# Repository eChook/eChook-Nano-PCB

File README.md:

# eChook Nano PCB

This is the RS DesignSpark PCB project file and associated gerber files and BOM for the eChook Nano PCB v1.1

eChook Specific Libraries not included yet.

Designspark 8 required

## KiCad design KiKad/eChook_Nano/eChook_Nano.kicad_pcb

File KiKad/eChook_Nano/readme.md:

V2.0a issues:
- Op Amp inputs switched. -FIXED 26/09
- TP Vias too small to capture multimeter probe tip. Fixed 26/09
- RPM inputs not working??
- No 24v power LED

V2.0b TODO
- Add 24v Indicator LED
- Make Throttle input 24v safe - 24mA through 200mA capable diode - TEST!
- THT Pads enlarged
- keep out zone around BT Mount point
- Totem Pole BAT54S diode protection on all inputs
-

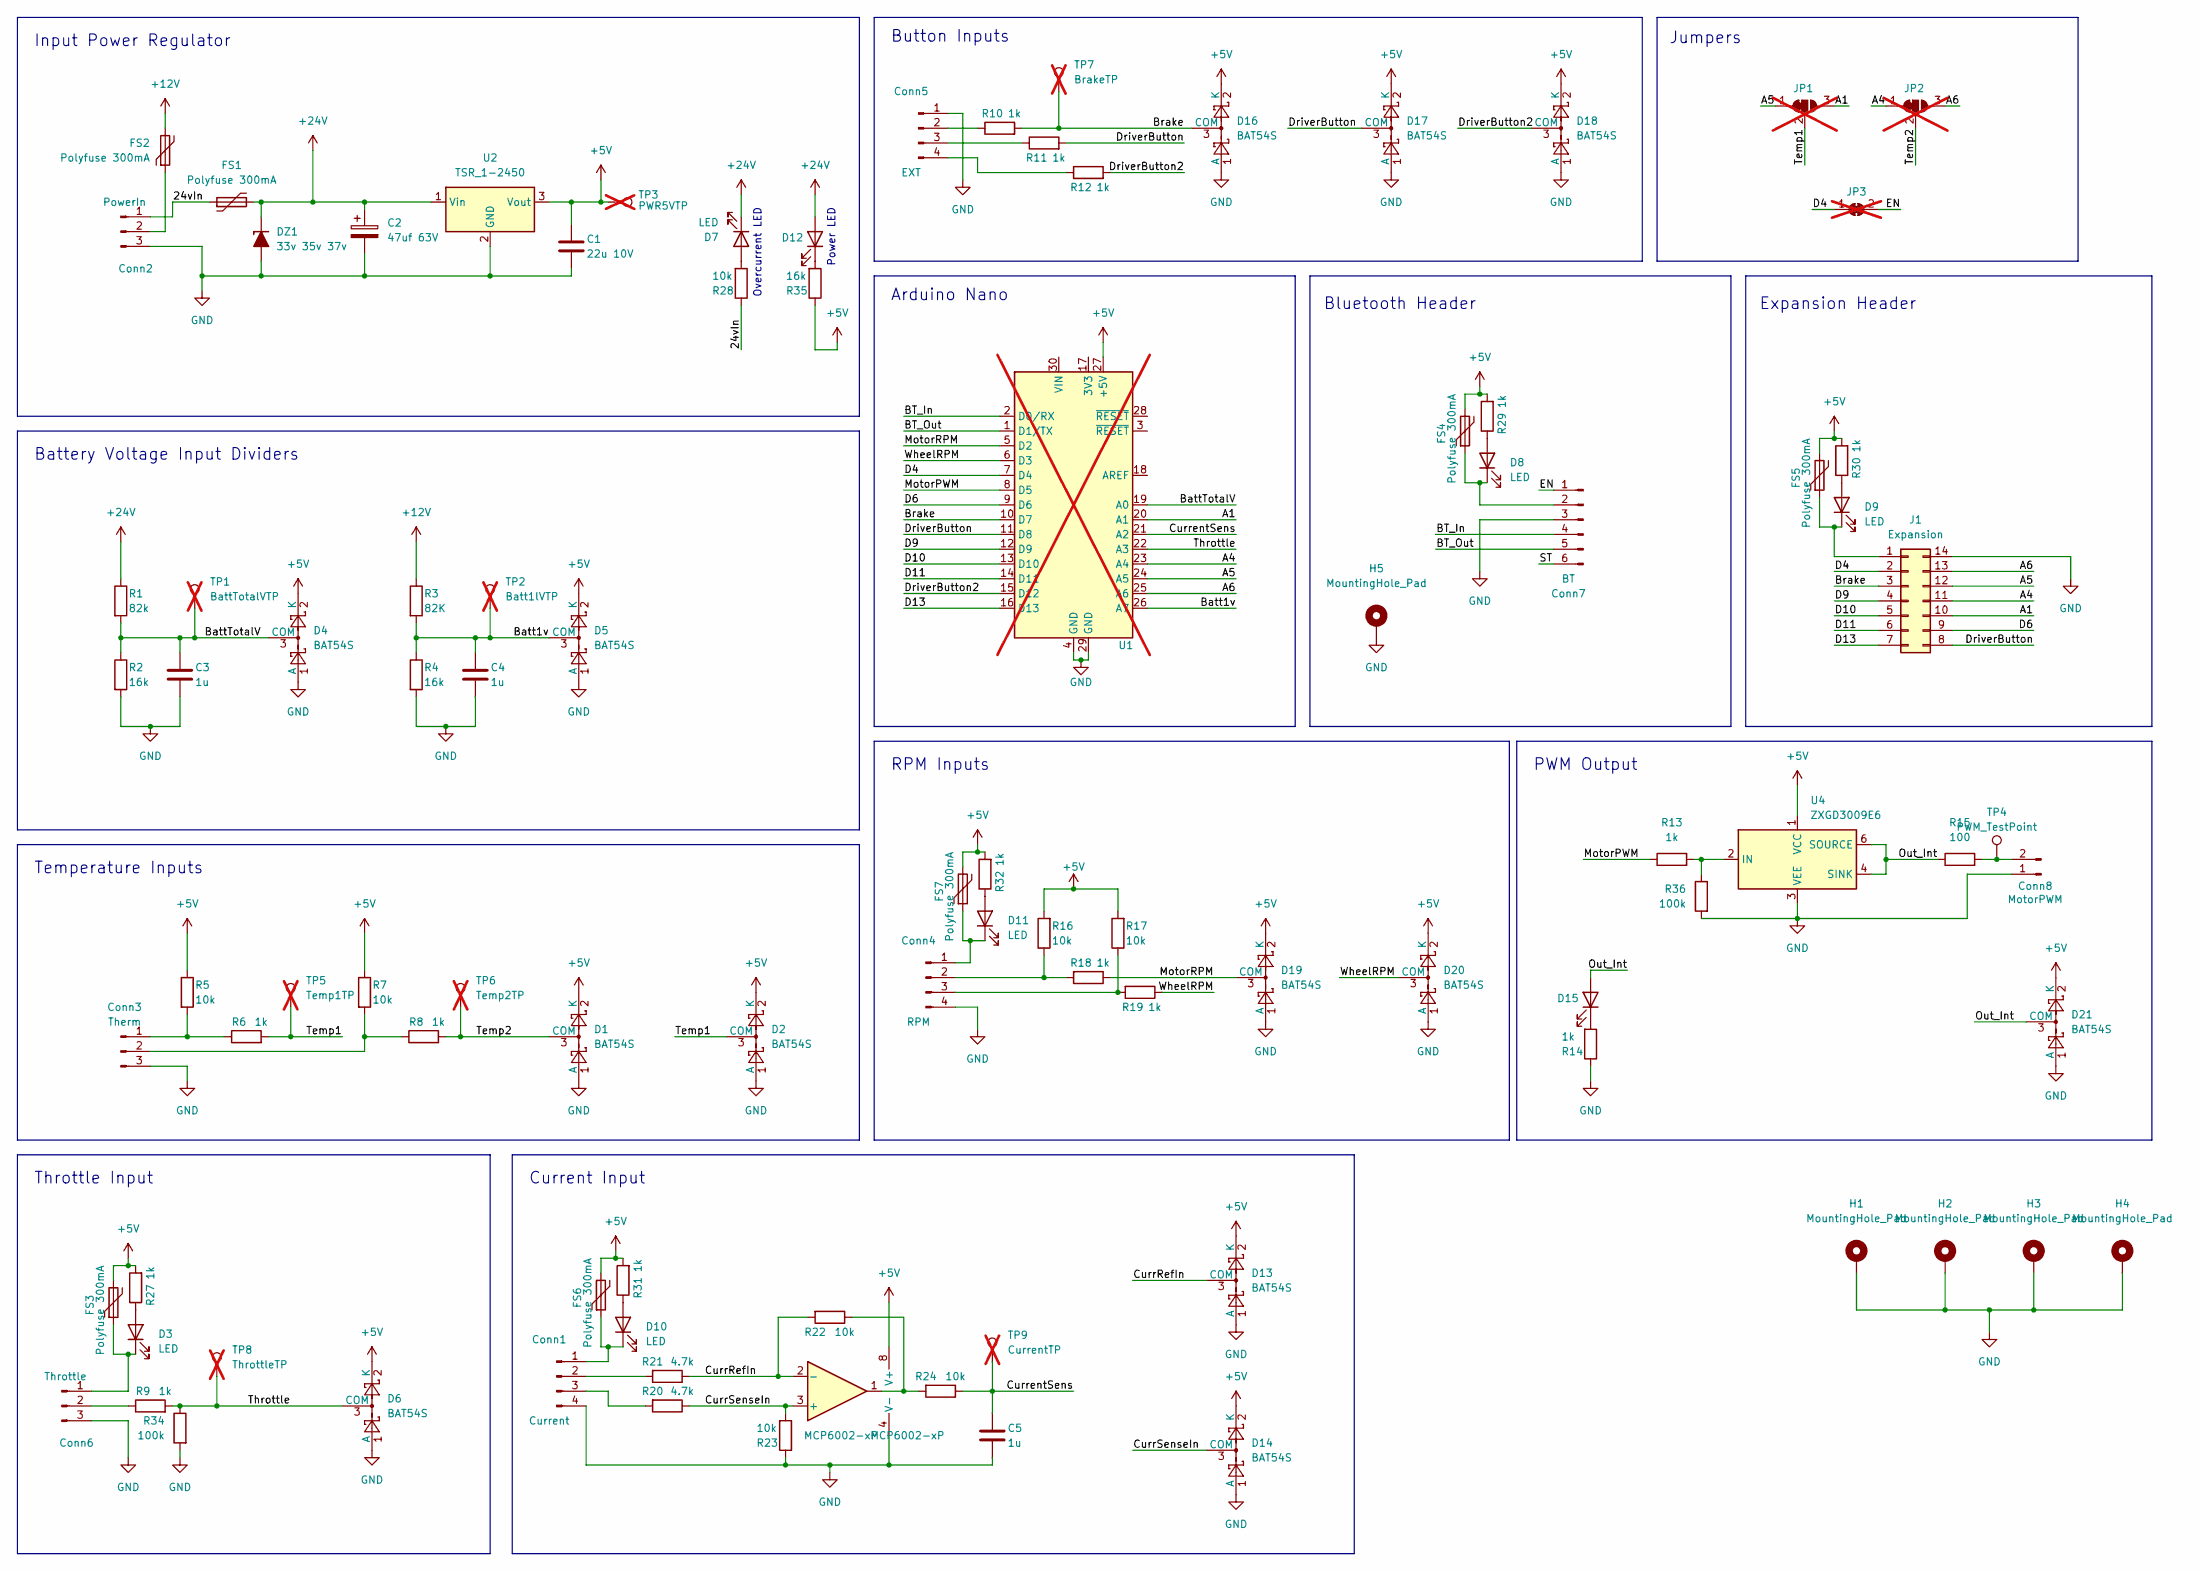
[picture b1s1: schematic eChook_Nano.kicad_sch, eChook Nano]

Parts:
C1: 22u 10V; C_0805_2012Metric; LCSC C45783
C2: 47uf 63V; CP_Elec_10x10; MPN EEEHA1J470P; LCSC C125977
C3, C4, C5: 1u; C_0805_2012Metric; LCSC C28323
Conn1: Current; Pluggable_Terminal_4_5.08mm; LCSC C8443
Conn2: PowerIn; Pluggable_Terminal_3_3.81mm; LCSC C8406
Conn3: Therm; Pluggable_Terminal_3_5.08mm; LCSC C70914
Conn4: RPM; Pluggable_Terminal_4_5.08mm; LCSC C8443
Conn5: EXT; Pluggable_Terminal_4_5.08mm; LCSC C8443
Conn6: Throttle; Pluggable_Terminal_3_5.08mm; LCSC C70914
Conn7: BT; PinHeader_1x06_P2.54mm_Vertical; LCSC C5224026
Conn8: MotorPWM; Pluggable_Terminal_2_5.08mm; LCSC C441204
D1, D2, D4, D5, D6, D13, D14, D16, D17, D18, D19, D20, D21: BAT54S; SOT-23; MPN BAT54S,215; LCSC C47546
D3, D7, D8, D9, D10, D11: LED; LED_0603_1608Metric; LCSC C2286
D12, D15: LED_GREEN; LED_0805_2012Metric; MPN KT-0805G; LCSC C2297
DZ1: 33v 35v 37v; D_SMB; MPN PTZTE2533B; LCSC C2909283
FS1, FS2, FS3, FS4, FS5, FS6, FS7: Polyfuse 300mA; Fuse_0603_1608Metric; MPN BHFUSE BSMD0603-010-36V; LCSC C7472522
H1, H2, H3, H4: MountingHole_Pad; MountingHole_3.2mm_M3_DIN965_Pad_TopBottom
H5: MountingHole_Pad; MountingHole_4.3mm_M4_DIN965_Pad
J1: Expansion; PinHeader_2x07_P2.54mm_Vertical; LCSC C38844
JP1, JP2: SolderJumper_3_Bridged12; SolderJumper-3_P1.3mm_Bridged12_RoundedPad1.0x1.5mm; not fitted
JP3: SolderJumper-2_P1.3mm_Bridged_RoundedPad1.0x1.5mm; not fitted
R1: 82k; R_0805_2012Metric; LCSC C21571501
R2, R4, R35: 16k; R_0805_2012Metric; LCSC C706220
R3: 82K; R_0805_2012Metric; LCSC C21571501
R5, R7, R16, R17, R22, R23, R24, R28: 10k; R_0805_2012Metric; LCSC C17414
R6, R8, R9, R10, R11, R12, R14, R18, R19, R27, R29, R30, R31, R32: 1k; R_0805_2012Metric; LCSC C17513
R13: 1k; R_0805_2012Metric; LCSC C17414
R15: 100; R_0805_2012Metric; LCSC C17414
R20, R21: 4.7k; R_0805_2012Metric; LCSC C17673
R34, R36: 100k; R_0805_2012Metric; LCSC C149504
TP1: BattTotalVTP; TestPoint_Pad_D3.0mm; not fitted
TP2: Batt1lVTP; TestPoint_Pad_D3.0mm; not fitted
TP3: PWR5VTP; TestPoint_Pad_D3.0mm; not fitted
TP4: PWM_TestPoint; TestPoint_Pad_D3.0mm
TP5: Temp1TP; TestPoint_Pad_D3.0mm; not fitted
TP6: Temp2TP; TestPoint_Pad_D3.0mm; not fitted
TP7: BrakeTP; TestPoint_Pad_D3.0mm; not fitted
TP8: ThrottleTP; TestPoint_Pad_D3.0mm; not fitted
TP9: CurrentTP; TestPoint_Pad_D3.0mm; not fitted
U1: Arduino_Nano_v3.x; Arduino_Nano; not fitted
U2: TSR_1-2450; Converter_DCDC_TRACO_TSR-1_THT; LCSC C19188491
U3: MCP6002-xP; SOIC-8_3.9x4.9mm_P1.27mm; LCSC C7377
U4: ZXGD3009E6; SOT-23-6; LCSC C156293

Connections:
+5V: C1.1, D1.2 (K), D2.2 (K), D4.2 (K), D5.2 (K), D6.2 (K), D13.2 (K), D14.2 (K), D16.2 (K), D17.2 (K), D18.2 (K), D19.2 (K), D20.2 (K), D21.2 (K), FS3.2, FS4.2, FS5.2, FS6.2, FS7.2, R5.1, R7.1, R16.2, R17.2, R27.2, R29.2, R30.2, R31.2, R32.2, R35.1, TP3.1, U1.27 (+5V), U2.3 (Vout), U3.8 (V+), U4.1 (VCC)
+12V: FS2.2, R3.1
+24V: C2.1, D7.1 (K), D12.2 (A), DZ1.1 (K), FS1.2, R1.1, U2.1 (Vin)
/24vIn: Conn2.1, FS1.1, R28.1
/A1: J1.10, JP1.3 (B), U1.20 (A1)
/A4: J1.11, JP2.1 (A), U1.23 (A4)
/A5: J1.12, JP1.1 (A), U1.24 (A5)
/A6: J1.13, JP2.3 (B), U1.25 (A6)
/BT_In: Conn7.4, U1.2 (D0/RX)
/BT_Out: Conn7.5, U1.1 (D1/TX)
/Batt1v: C4.1, D5.3 (COM), R3.2, R4.1, TP2.1, U1.26 (A7)
/BattTotalV: C3.1, D4.3 (COM), R1.2, R2.1, TP1.1, U1.19 (A0)
/Brake: D16.3 (COM), J1.3, R10.2, TP7.1, U1.10 (D7)
/CurrRefIn: D13.3 (COM), R21.1, R22.2, U3.2 (-)
/CurrSenseIn: D14.3 (COM), R20.1, R23.2, U3.3 (+)
/CurrentSens: C5.1, R24.1, TP9.1, U1.21 (A2)
/D4: J1.2, JP3.1 (A), U1.7 (D4)
/D6: J1.9, U1.9 (D6)
/D9: J1.4, U1.12 (D9)
/D10: J1.5, U1.13 (D10)
/D11: J1.6, U1.14 (D11)
/D13: J1.7, U1.16 (D13)
/DriverButton: D17.3 (COM), J1.8, R11.2, U1.11 (D8)
/DriverButton2: D18.3 (COM), R12.2, U1.15 (D12)
/EN: Conn7.1, JP3.2 (B)
/MotorPWM: R13.1, U1.8 (D5)
/MotorRPM: D19.3 (COM), R18.1, U1.5 (D2)
/Out_Int: D15.2 (A), D21.3 (COM), R15.1, U4.4 (SINK), U4.6 (SOURCE)
/ST: Conn7.6
/Temp1: D2.3 (COM), JP1.2 (C), R6.2, TP5.1
/Temp2: D1.3 (COM), JP2.2 (C), R8.2, TP6.1
/Throttle: D6.3 (COM), R9.2, R34.1, TP8.1, U1.22 (A3)
/WheelRPM: D20.3 (COM), R19.1, U1.6 (D3)
GND: C1.2, C2.2, C3.2, C4.2, C5.2, Conn1.4, Conn2.3, Conn3.3, Conn4.4, Conn5.1, Conn6.3, Conn7.3, Conn8.1, D1.1 (A), D2.1 (A), D4.1 (A), D5.1 (A), D6.1 (A), D13.1 (A), D14.1 (A), D16.1 (A), D17.1 (A), D18.1 (A), D19.1 (A), D20.1 (A), D21.1 (A), DZ1.2 (A), H1.1, H2.1, H3.1, H4.1, H5.1, J1.14, R2.2, R4.2, R14.1, R23.1, R34.2, R36.2, U1.4 (GND), U1.29 (GND), U2.2 (GND), U3.4 (V-), U4.3 (VEE)
unnamed: Conn1.1, D10.1 (K), FS6.1
unnamed: Conn1.2, R21.2
unnamed: Conn1.3, R20.2
unnamed: Conn2.2, FS2.1
unnamed: Conn3.1, R5.2, R6.1
unnamed: Conn3.2, R7.2, R8.1
unnamed: Conn4.1, D11.1 (K), FS7.1
unnamed: Conn4.2, R16.1, R18.2
unnamed: Conn4.3, R17.1, R19.2
unnamed: Conn5.2, R10.1
unnamed: Conn5.3, R11.1
unnamed: Conn5.4, R12.1
unnamed: Conn6.1, D3.1 (K), FS3.1
unnamed: Conn6.2, R9.1
unnamed: Conn7.2, D8.1 (K), FS4.1
unnamed: Conn8.2, R15.2, TP4.1
unnamed: D3.2 (A), R27.1
unnamed: D7.2 (A), R28.2
unnamed: D8.2 (A), R29.1
unnamed: D9.2 (A), R30.1
unnamed: D9.1 (K), FS5.1, J1.1
unnamed: D10.2 (A), R31.1
unnamed: D11.2 (A), R32.1
unnamed: D12.1 (K), R35.2
unnamed: D15.1 (K), R14.2
unnamed: R22.1, R24.2, U3.1
unnamed: R13.2, R36.1, U4.2 (IN)

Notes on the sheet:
Bluetooth Header
Input Power Regulator
Throttle Input
RPM Inputs
Arduino Nano
PWM Output
Power LED
Temperature Inputs
Current Input
Button Inputs
Overcurrent LED
Expansion Header
Jumpers
Battery Voltage Input Dividers

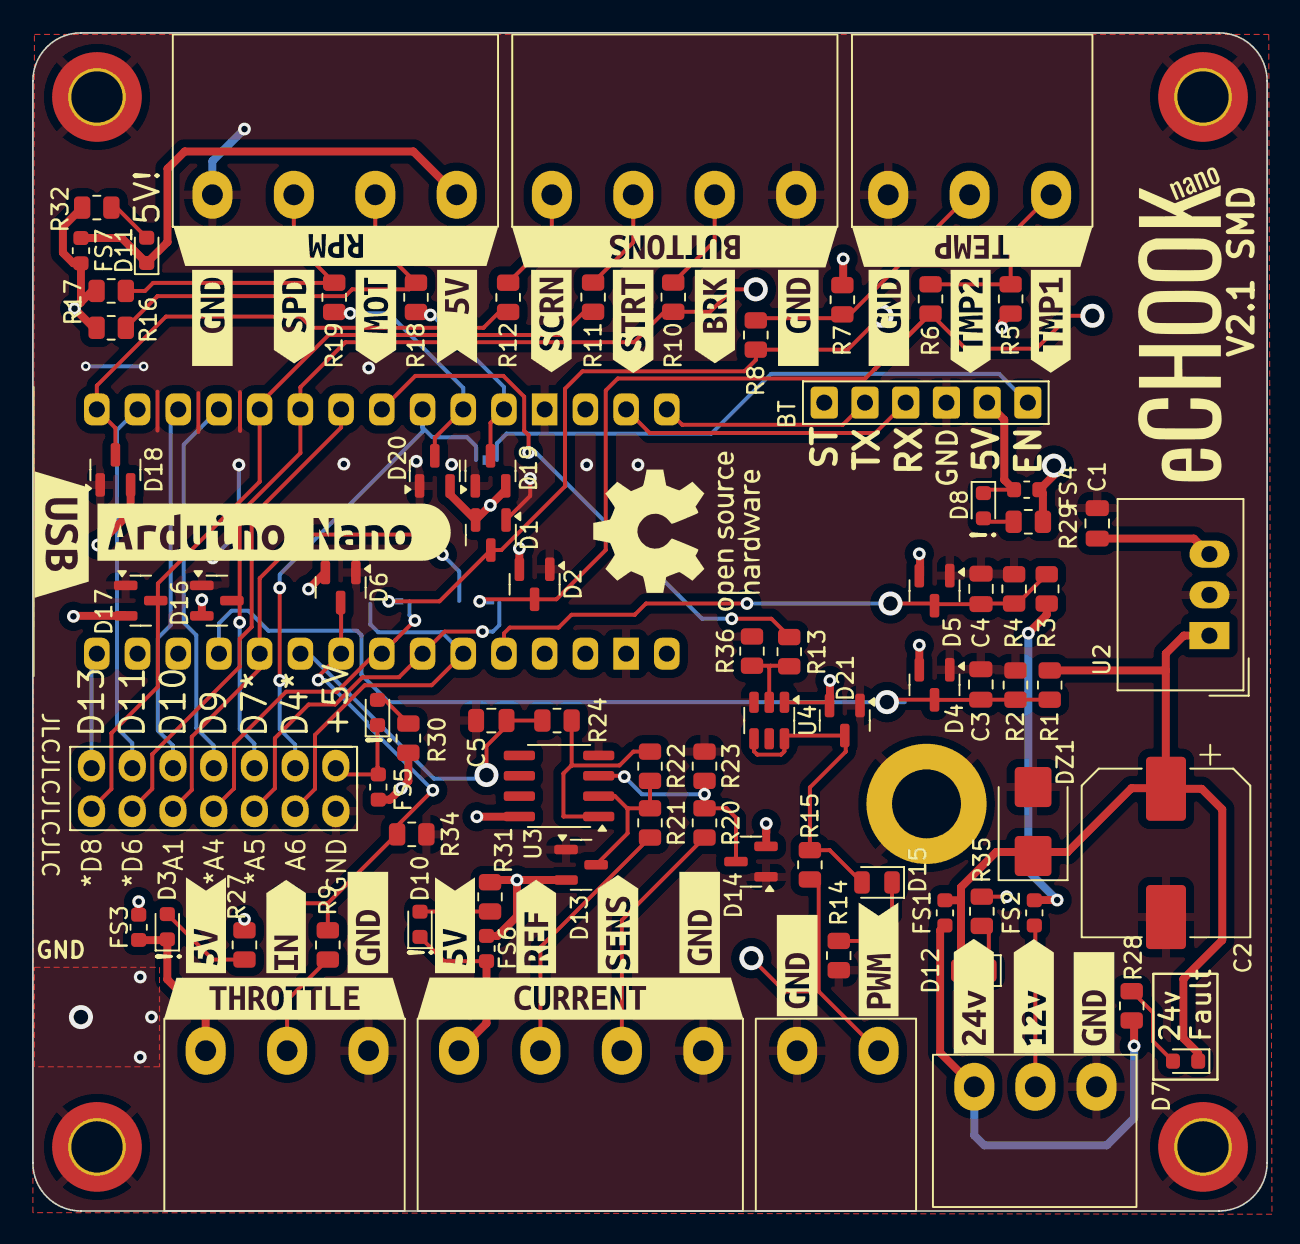
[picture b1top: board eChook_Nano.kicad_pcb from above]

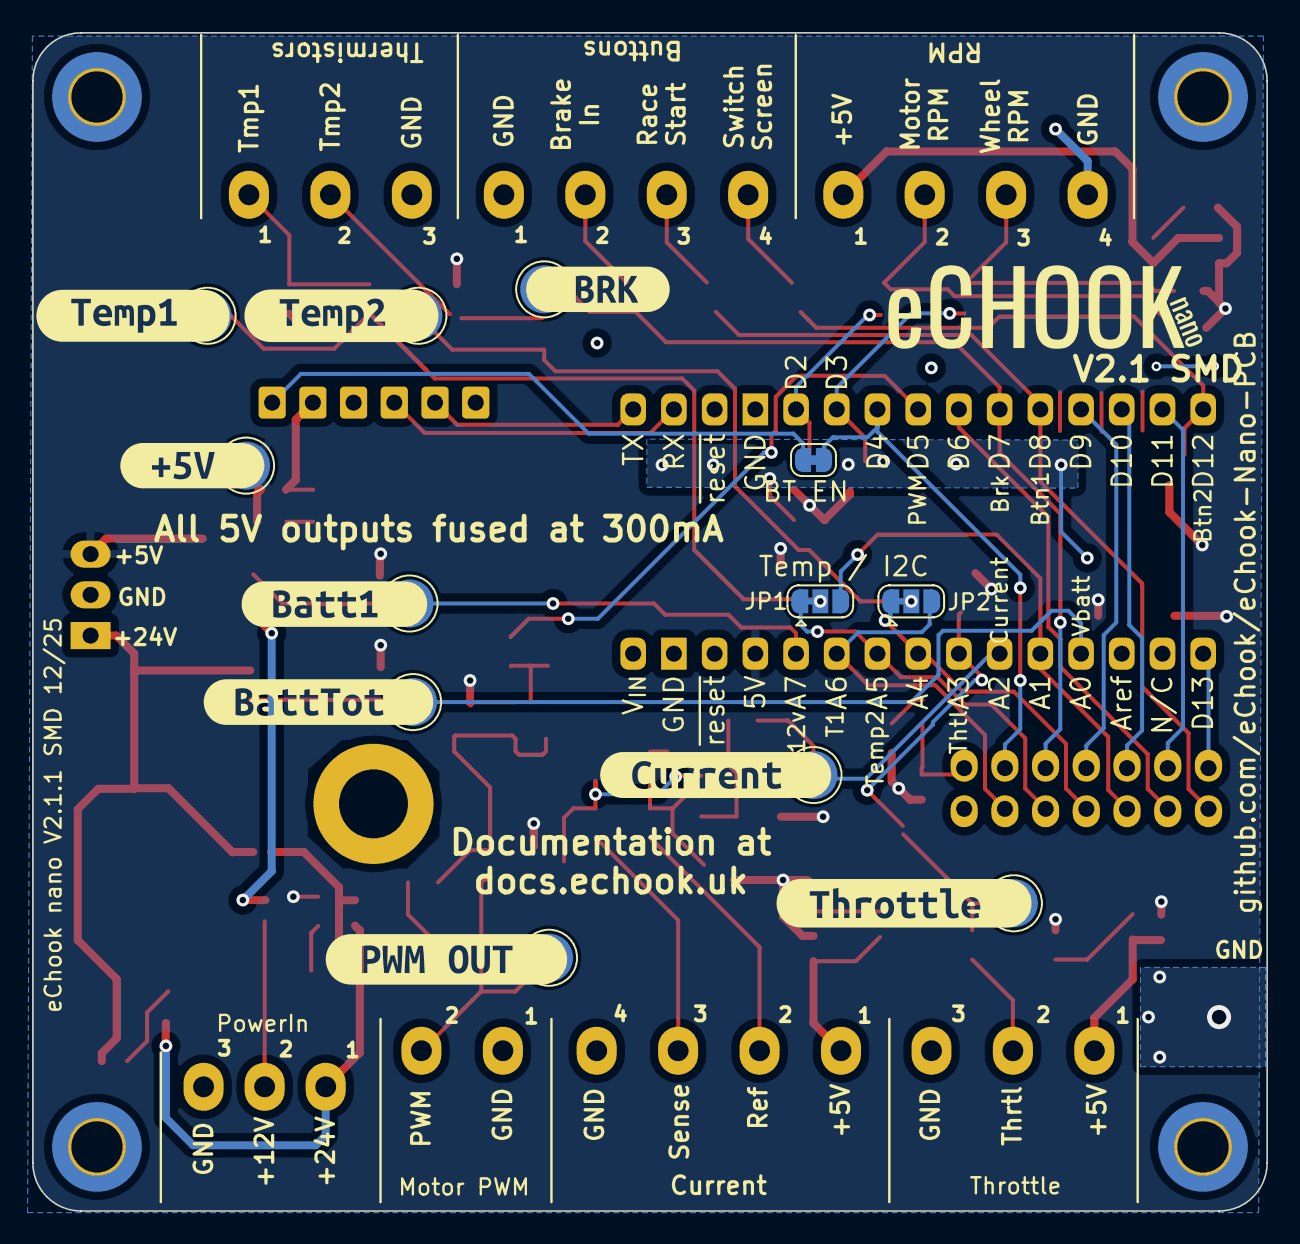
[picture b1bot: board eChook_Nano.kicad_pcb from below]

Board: 2 copper layers, 77.0 x 73.5 mm, 138 parts (21 on the bottom side), 60 nets.

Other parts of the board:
BC1, BC2: BOM-Component
kibuzzard-66D71FF8: G***; kibuzzard-66D71FF8
kibuzzard-66D72A35: G***; kibuzzard-66D72A35
kibuzzard-66D86D8A: G***; kibuzzard-66D86D8A
kibuzzard-66D86D91: G***; kibuzzard-66D86D91
kibuzzard-66D86E8F: G***; kibuzzard-66D86E8F
kibuzzard-66D86EA3: G***; kibuzzard-66D86EA3
kibuzzard-66D86EBA: G***; kibuzzard-66D86EBA
kibuzzard-66D86EDC: G***; kibuzzard-66D86EDC
kibuzzard-66D86F00: G***; kibuzzard-66D86F00
kibuzzard-66D86F2B: G***; kibuzzard-66D86F2B
kibuzzard-66D86F7C: G***; kibuzzard-66D86F7C
kibuzzard-66D86F40: G***; kibuzzard-66D86F40
kibuzzard-66D86F46: G***; kibuzzard-66D86F46
kibuzzard-66D86F51: G***; kibuzzard-66D86F51
kibuzzard-66D86F60: G***; kibuzzard-66D86F60
kibuzzard-66D727FC: G***; kibuzzard-66D727FC
kibuzzard-66D728C6: G***; kibuzzard-66D728C6
kibuzzard-66D728F7: G***; kibuzzard-66D728F7
kibuzzard-66D7200F: G***; kibuzzard-66D7200F
kibuzzard-66D7283F: G***; kibuzzard-66D7283F
kibuzzard-66D72019, kibuzzard-66D72019#2, kibuzzard-66D72019#3, kibuzzard-66D72019#4: G***; kibuzzard-66D72019
kibuzzard-66D72322: G***; kibuzzard-66D72322
kibuzzard-66D72613, kibuzzard-66D72613#2: G***; kibuzzard-66D72613
kibuzzard-66D72997: G***; kibuzzard-66D72997
kibuzzard-66E1D05B: G***; kibuzzard-66E1D05B
kibuzzard-66E1D172: G***; kibuzzard-66E1D172
kibuzzard-66E1DBD4: G***; kibuzzard-66E1DBD4
kibuzzard-66E1DC01: G***; kibuzzard-66E1DC01
kibuzzard-66E1DD3E: G***; kibuzzard-66E1DD3E
kibuzzard-66E1DD07: G***; kibuzzard-66E1DD07
kibuzzard-66E1DD26: G***; kibuzzard-66E1DD26
kibuzzard-66E1DDEC: G***; kibuzzard-66E1DDEC
kibuzzard-66E1DE80: G***; kibuzzard-66E1DE80
kibuzzard-66E1DE99: G***; kibuzzard-66E1DE99
kibuzzard-67D9A076: G***; kibuzzard-67D9A076

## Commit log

2017-06-07 initial commit of V1.1
2017-06-08 Added BOM
2017-07-06 Updated to latest PCB design
2017-07-28 V1.2 - improved solder mask tolerances, added test points and silkscreen logo
2017-08-23 Updated PCB Version in Readme
2017-09-04 Added GNU Licence.txt
2022-01-04 Restructured Filesystem. Started KiCad Recreation
2022-01-04 Add KiCad gitignore
2022-01-10 Finished PCB Replication, added iBOM
2022-01-12 Added 3D models and layout/silkscreen improvements
2022-01-12 Added 3D models
2022-01-15 Fixed Silkscreen Current Conn Pin Out
2022-02-14 Updated ext. pin out
2022-03-14 R15 and R24 Value Correction, new IBOM
2024-09-03 SMD Conversion
2024-09-04 Routing Complete
2024-09-04 connector Labels corrected
2024-09-11 Added ground plane under nano
2024-09-11 production ready
2024-09-12 Marked Alpha board, improved rotations
2024-09-26 Fixing V2.0a issues
2024-09-30 Updated to BAT54S diodes. Added protection on all inputs
2024-10-01 Layout and Silkscreen tweaks
2024-10-01 Reduced BT Support Hole to 3.2mm
2024-10-02 Back to M4 Mount for BT Support
2024-10-10 As ordered, 10/10/24
2024-12-17 Added gerbers for V1.3
2025-03-18 Updated Resistor values for PWM Out
2025-03-18 Added gate driver PWM output stage
2025-03-20 Increased PWR LED Resistance, Added mounting holes to SCH
2025-03-20 Fixed Mounting hole positions
2025-06-09 As manufactured V2.1
2025-12-13 24v LED fixed. Improved Routing and Labels
2025-12-17 As Manufactured 12/25
